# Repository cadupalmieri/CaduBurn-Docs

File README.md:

# CaduBurn
Repositório dedicado ao projeto e documentação do gravador de bootloader para microcontroladores de placas Arduino Compatível

- [1 - A Placa](https://github.com/cadupalmieri/CaduBurn/tree/master/2%20-%20A%20placa)
  - [1.1 - Surgimento](https://github.com/cadupalmieri/CaduBurn-Docs/tree/master/1%20-%20A%20Placa)
  - [1.2 - Lista de Material](https://github.com/cadupalmieri/CaduBurn-Docs/tree/master/1%20-%20A%20Placa)
  - [1.3 - Montagem](https://github.com/cadupalmieri/CaduBurn-Docs/tree/master/1%20-%20A%20Placa)
  
 - [2 - Instruções de Uso](https://github.com/cadupalmieri/CaduBurn-Docs/tree/master/2%20-%20Instruc%CC%A7o%CC%83es%20de%20Uso)  
    - [2.1 - Instalando os Drivers](https://github.com/cadupalmieri/CaduBurn-Docs/tree/master/2%20-%20Instruc%CC%A7o%CC%83es%20de%20Uso)
    - [2.2 - Configurando Arduino como gravador](https://github.com/cadupalmieri/CaduBurn-Docs/tree/master/2%20-%20Instruc%CC%A7o%CC%83es%20de%20Uso)
    - [2.3 - Gravando o bootloader no microncontrolador](https://github.com/cadupalmieri/CaduBurn-Docs/tree/master/2%20-%20Instruc%CC%A7o%CC%83es%20de%20Uso)

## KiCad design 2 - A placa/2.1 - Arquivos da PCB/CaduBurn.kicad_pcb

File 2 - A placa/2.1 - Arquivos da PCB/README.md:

Arquivos do projeto e design da PCB para o SW Kicad

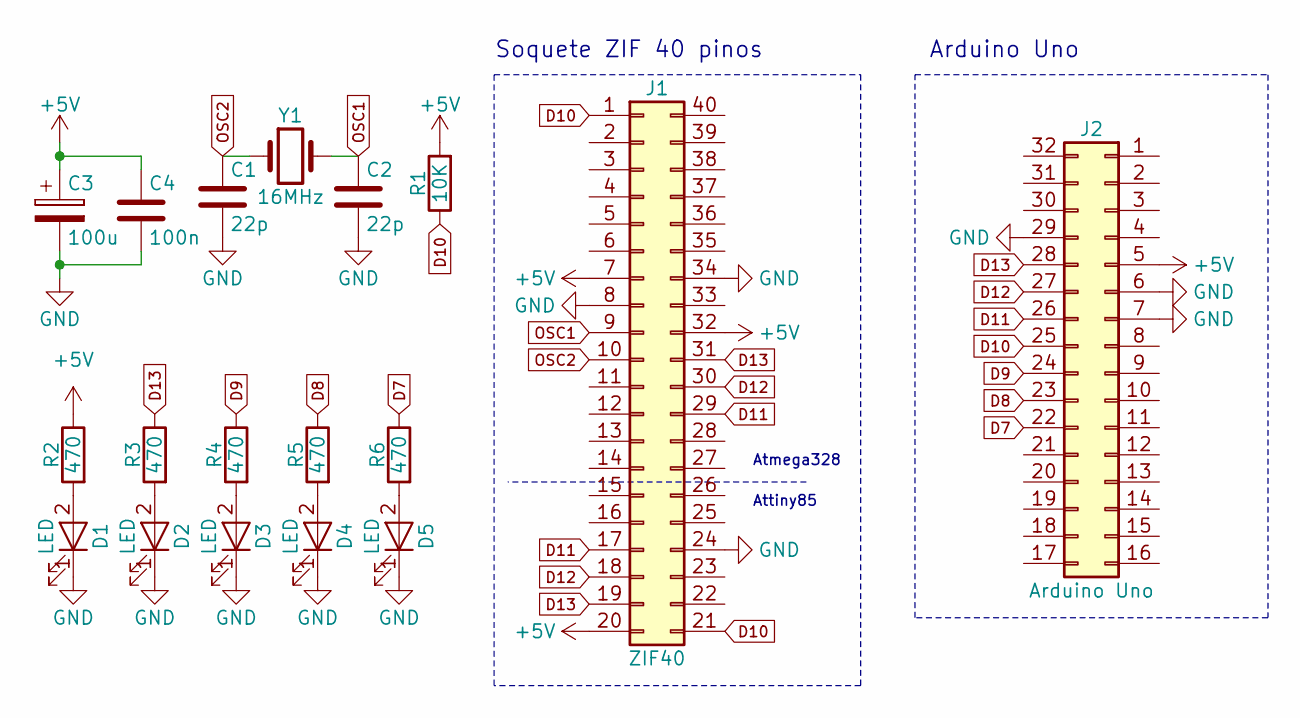
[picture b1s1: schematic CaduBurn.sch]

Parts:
C1, C2: 22p; C_Disc_D3.0mm_W1.6mm_P2.50mm
C3: 100u; CP_Radial_D4.0mm_P2.00mm
C4: 100n; C_Disc_D3.0mm_W1.6mm_P2.50mm
D1, D2, D3, D4, D5: LED; LED_D3.0mm
J1: ZIF40; DIP-40_W15.24mm_LongPads
J2: Arduino Uno; Arduino_UNO_R3_WithMountingHoles
R1: 10K; R_Axial_DIN0207_L6.3mm_D2.5mm_P10.16mm_Horizontal
R2, R3, R4, R5, R6: 470; R_Axial_DIN0207_L6.3mm_D2.5mm_P10.16mm_Horizontal
Y1: 16MHz; Crystal_HC49-4H_Vertical

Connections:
+5V: C3.1, C4.1, J1.7, J1.20, J1.32, J2.5, R1.2, R2.1
D7: J2.22, R6.1
D8: J2.23, R5.1
D9: J2.24, R4.1
D10: J1.1, J1.21, J2.25, R1.1
D11: J1.17, J1.29, J2.26
D12: J1.18, J1.30, J2.27
D13: J1.19, J1.31, J2.28, R3.1
GND: C1.2, C2.2, C3.2, C4.2, D1.1 (K), D2.1 (K), D3.1 (K), D4.1 (K), D5.1 (K), J1.8, J1.24, J1.34, J2.6, J2.7, J2.29
unnamed: D1.2 (A), R2.2
unnamed: D2.2 (A), R3.2
unnamed: D3.2 (A), R4.2
unnamed: D4.2 (A), R5.2
unnamed: D5.2 (A), R6.2
OSC1: C2.1, J1.9, Y1.2
OSC2: C1.1, J1.10, Y1.1

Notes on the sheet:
Atmega328
Attiny85
Soquete ZIF 40 pinos
Arduino Uno

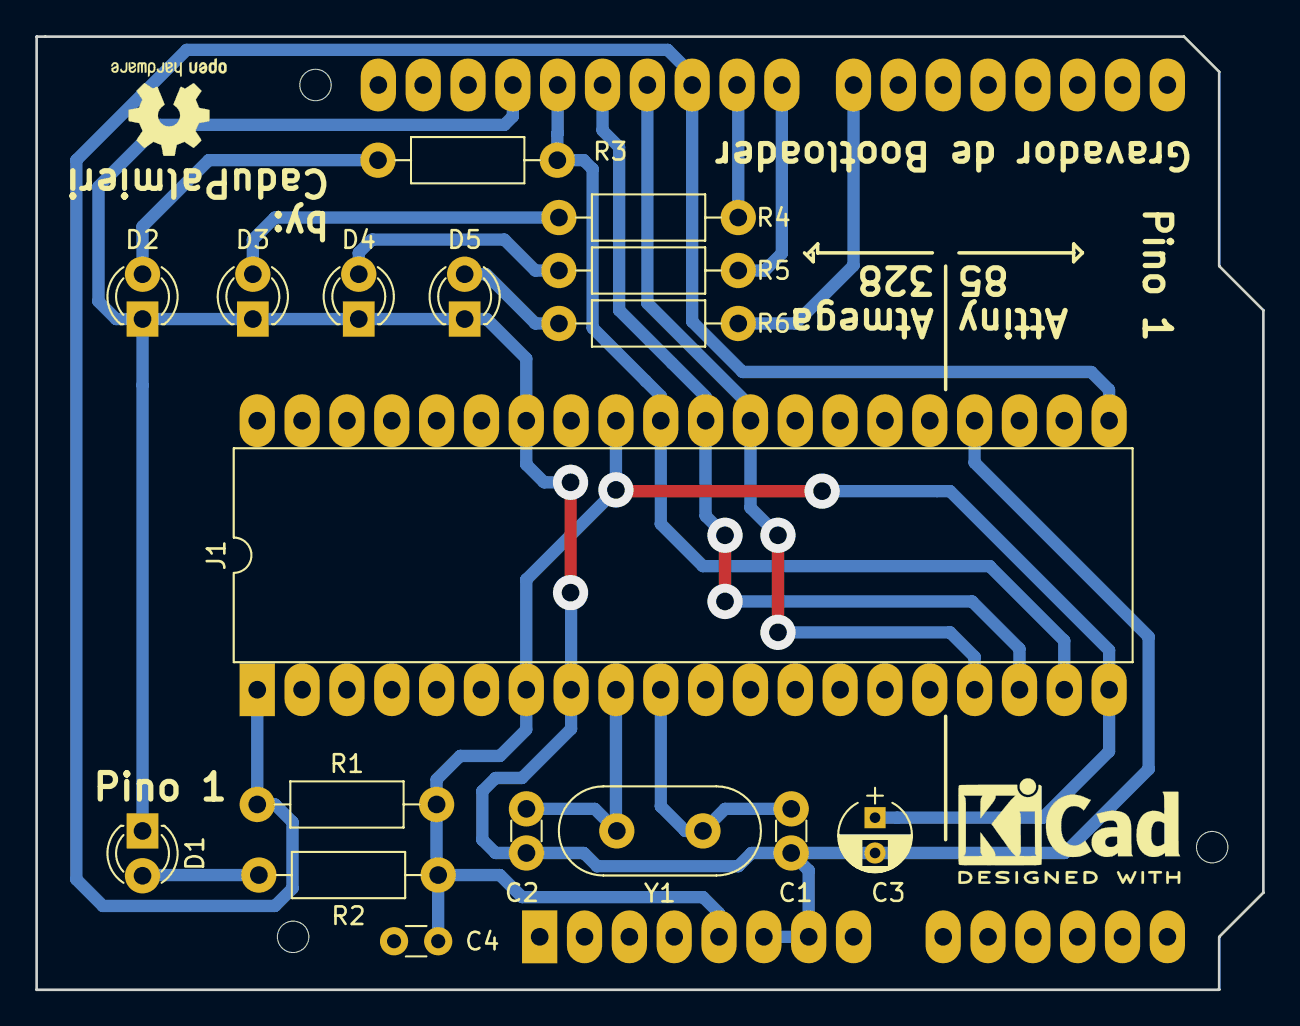
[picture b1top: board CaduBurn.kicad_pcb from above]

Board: 2 copper layers, 69.5 x 54.0 mm, 18 parts (1 on the bottom side), 16 nets.

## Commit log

2018-06-05 Add files via upload
    Images
2018-07-01 Update README.md
    formatação
